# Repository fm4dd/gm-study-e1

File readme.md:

## GM-STUDY-E1

### Description

The gm-study-e1 board is an application module board for the <a href="https://www.colognechip.com/programmable-logic/gatemate-evaluation-board/">GateMate FPGA evaluation board E1</a>, made by <a href="https://www.colognechip.com/">Cologne Chip</a>. It connects to the evaluation board through all six GPIO headers, and its main feature are the input/output components similar to popular FPGA trainer boards used for classroom teaching in electrical engineering and embedded systems education (e.g. Digilent Basys or Altera DE10-lite). These boards were created after successful design tests of the <a href="https://github.com/fm4dd/gm-proto-e1">gm-proto-e1</a> boards. The "gm-proto-e1" boards have only a few basic I/O, but provide a 2.54mm prototyping area for experimentation with GateMate E1.

### Overview

The gm-study-e1 boards provide:
- 4x push buttons
- 10x slide switches
- 10x LED
- 6x 7-Segment display modules (non-multiplexed)
- 1x 4 Khz buzzer
- J1 2.54mm pin header with 5V signal translation

The J1 pin header and pinout can connect 5V HD44780 character LCD display modules, or interface with breadboards for prototyping. There, the FPGA 2.5V IO signals are translated into 5V TTL levels, which can be used with an Arduino.

This design is registered under the OSHWA Open Source Hardware Self-Certification:  

### Hardware Versions

Two board variants have been designed: SMD, using 0.28" SMD 7-Segment modules, and THT for using slightly bigger 0.3" through-hole 7-Segment modules. For THT components, great care needs to be taken to cut pins flush during soldering, and prevent them from reaching components of the evaluation board below. The 1.27mm pitch GPIO connectors are offered with different distance spacers (2, 2.5 and 5mm), and the standard spacers achieve only 5mm total clearance.

Both gm-study-e1 application boards have been designed as a 100x70mm double-layer PCB with precision alignment of the six 46-pin 1.27mm pitch GPIO bank connectors (mates all 276 pins with the GateMate FPGA evaluation board E1 V3.1B).

#### Through-hole Design:

| Version | Gerber | Schema |
|---------|--------|--------|
| 1.1     |[2030325-gm-study-e1-tht-gerber.zip](fabfiles-tht/v11/20230325-gm-study-e1-tht-gerber.zip) | [20230325-gm-proto-e1-schematic.pdf](fabfiles-tht/v11/20230325-gm-study-e1-tht-schematic.pdf) |

#### Surface-Mount Design:

| Version | Gerber | Schema |
|---------|--------|--------|
| 1.1     |[20230326-gm-study-e1-smd-gerber.zip](fabfiles-smd/v11/20230326-gm-study-e1-smd-gerber.zip) | [20230326-gm-study-e1-smd-schematic.pdf](fabfiles-smd/v11/20230326-gm-study-e1-smd-schematic.pdf) |

### Pin Assignments

Both variants (THT and SMD) have identical pinout, listed in [pin-assignment.md](pin-assignment.md).
They share a single constraints assignment file, located here: [gm-study-e1.ccf](examples/gm-study-e1.ccf)

### Example Code

The following code examples demonstrate the board input/output components for quick verification. The code has been tested with the pre-compiled opensource toolchain released through the GateMate support site at <a href="https://www.colognechip.com/mygatemate/">https://www.colognechip.com/mygatemate/</a>

| Language | Folder                   | Description                                                       |
|----------|--------------------------|-------------------------------------------------------------------|
| Verilog  |[blink](examples/blink)   | blinks five LED's in a alternating pattern                        |
| Verilog  |[count](examples/count)   | binary counter displayed on ten LED and six 7-Segment digits      |
| Verilog  |[button](examples/button) | push button press changes LED frequency and light move direction  |
| Verilog  |[switch](examples/switch) | each slide switch turns its corresponding LED on or off           |
| Verilog  |[sound](examples/sound)   | play a song on the buzzer, show notes on LED and 7-segment digits |

### Board Pictures

The gm-study-e1 application board, running the switch demo.

The gm-study-e1 application board has been designed with KiCad version 6.0.

The gm-study-e1 application board, up close.

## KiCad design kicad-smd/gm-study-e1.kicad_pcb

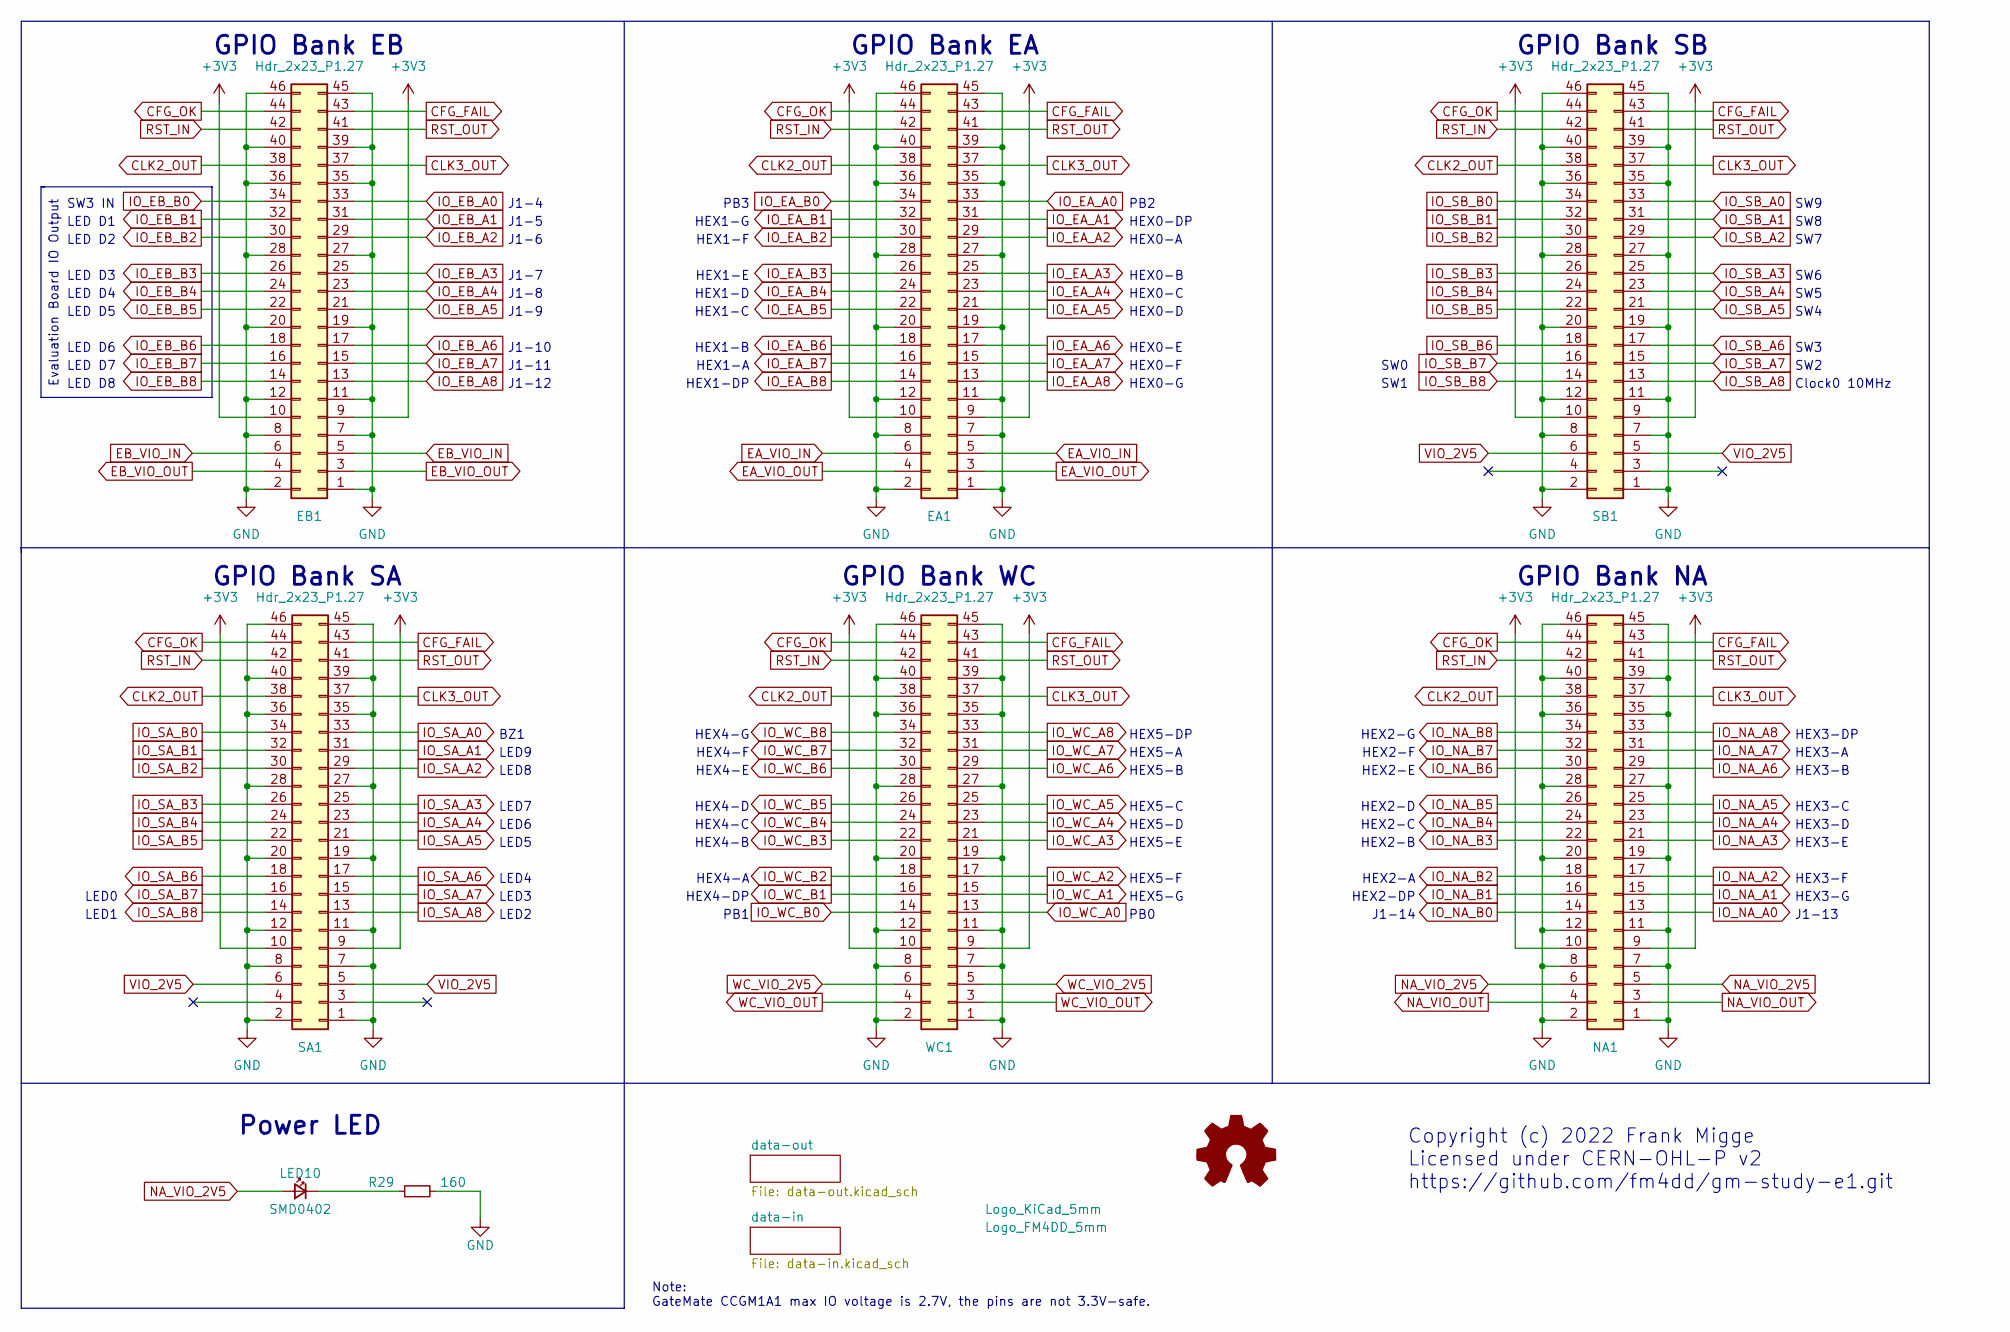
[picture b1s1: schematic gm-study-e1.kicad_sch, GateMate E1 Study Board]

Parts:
EA1: Hdr_2x23_P1.27; PinHeader_2x23_P1.27_backside
EB1: Hdr_2x23_P1.27; PinHeader_2x23_P1.27_backside
LB1: Logo_KiCad_5mm; Logo_KiCad_5mm_SScr
LB2: Label_5V
LB3: Label_GND
LB4: Logo_FM4DD_5mm; Logo_FM4DD_5mm_SScr
LED10: SMD0402; LED_0402_no_frame
NA1: Hdr_2x23_P1.27; PinHeader_2x23_P1.27_backside
R29: 160; R_0402_1005Metric
SA1: Hdr_2x23_P1.27; PinHeader_2x23_P1.27_backside
SB1: Hdr_2x23_P1.27; PinHeader_2x23_P1.27_backside
WC1: Hdr_2x23_P1.27; PinHeader_2x23_P1.27_backside

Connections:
+3V3: EA1.9, EA1.10, EB1.9, EB1.10, NA1.9, NA1.10, SA1.9, SA1.10, SB1.9, SB1.10, WC1.9, WC1.10; also elsewhere on the board
CFG_FAIL: EA1.43, EB1.43, NA1.43, SA1.43, SB1.43, WC1.43
CFG_OK: EA1.44, EB1.44, NA1.44, SA1.44, SB1.44, WC1.44
CLK2_OUT: EA1.38, EB1.38, NA1.38, SA1.38, SB1.38, WC1.38
CLK3_OUT: EA1.37, EB1.37, NA1.37, SA1.37, SB1.37, WC1.37
EA_VIO_IN: EA1.5, EA1.6
EA_VIO_OUT: EA1.3, EA1.4
EB_VIO_IN: EB1.5, EB1.6; also elsewhere on the board
EB_VIO_OUT: EB1.3, EB1.4
GND: EA1.1, EA1.2, EA1.7, EA1.8, EA1.11, EA1.12, EA1.19, EA1.20, EA1.27, EA1.28, EA1.35, EA1.36, EA1.39, EA1.40, EA1.45, EA1.46, EB1.1, EB1.2, EB1.7, EB1.8, EB1.11, EB1.12, EB1.19, EB1.20, EB1.27, EB1.28, EB1.35, EB1.36, EB1.39, EB1.40, EB1.45, EB1.46, NA1.1, NA1.2, NA1.7, NA1.8, NA1.11, NA1.12, NA1.19, NA1.20, NA1.27, NA1.28, NA1.35, NA1.36, NA1.39, NA1.40, NA1.45, NA1.46, R29.2, SA1.1, SA1.2, SA1.7, SA1.8, SA1.11, SA1.12, SA1.19, SA1.20, SA1.27, SA1.28, SA1.35, SA1.36, SA1.39, SA1.40, SA1.45, SA1.46, SB1.1, SB1.2, SB1.7, SB1.8, SB1.11, SB1.12, SB1.19, SB1.20, SB1.27, SB1.28, SB1.35, SB1.36, SB1.39, SB1.40, SB1.45, SB1.46, WC1.1, WC1.2, WC1.7, WC1.8, WC1.11, WC1.12, WC1.19, WC1.20, WC1.27, WC1.28, WC1.35, WC1.36, WC1.39, WC1.40, WC1.45, WC1.46; also elsewhere on the board
IO_EA_A0: EA1.33; also elsewhere on the board
IO_EA_A1: EA1.31; also elsewhere on the board
IO_EA_A2: EA1.29; also elsewhere on the board
IO_EA_A3: EA1.25; also elsewhere on the board
IO_EA_A4: EA1.23; also elsewhere on the board
IO_EA_A5: EA1.21; also elsewhere on the board
IO_EA_A6: EA1.17; also elsewhere on the board
IO_EA_A7: EA1.15; also elsewhere on the board
IO_EA_A8: EA1.13; also elsewhere on the board
IO_EA_B0: EA1.34; also elsewhere on the board
IO_EA_B1: EA1.32; also elsewhere on the board
IO_EA_B2: EA1.30; also elsewhere on the board
IO_EA_B3: EA1.26; also elsewhere on the board
IO_EA_B4: EA1.24; also elsewhere on the board
IO_EA_B5: EA1.22; also elsewhere on the board
IO_EA_B6: EA1.18; also elsewhere on the board
IO_EA_B7: EA1.16; also elsewhere on the board
IO_EA_B8: EA1.14; also elsewhere on the board
IO_EB_A0: EB1.33; also elsewhere on the board
IO_EB_A1: EB1.31; also elsewhere on the board
IO_EB_A2: EB1.29; also elsewhere on the board
IO_EB_A3: EB1.25; also elsewhere on the board
IO_EB_A4: EB1.23; also elsewhere on the board
IO_EB_A5: EB1.21; also elsewhere on the board
IO_EB_A6: EB1.17; also elsewhere on the board
IO_EB_A7: EB1.15; also elsewhere on the board
IO_EB_A8: EB1.13; also elsewhere on the board
IO_EB_B0: EB1.34
IO_EB_B1: EB1.32
IO_EB_B2: EB1.30
IO_EB_B3: EB1.26
IO_EB_B4: EB1.24
IO_EB_B5: EB1.22
IO_EB_B6: EB1.18
IO_EB_B7: EB1.16
IO_EB_B8: EB1.14
IO_NA_A0: NA1.13; also elsewhere on the board
IO_NA_A1: NA1.15; also elsewhere on the board
IO_NA_A2: NA1.17; also elsewhere on the board
IO_NA_A3: NA1.21; also elsewhere on the board
IO_NA_A4: NA1.23; also elsewhere on the board
IO_NA_A5: NA1.25; also elsewhere on the board
IO_NA_A6: NA1.29; also elsewhere on the board
IO_NA_A7: NA1.31; also elsewhere on the board
IO_NA_A8: NA1.33; also elsewhere on the board
IO_NA_B0: NA1.14; also elsewhere on the board
IO_NA_B1: NA1.16; also elsewhere on the board
IO_NA_B2: NA1.18; also elsewhere on the board
IO_NA_B3: NA1.22; also elsewhere on the board
IO_NA_B4: NA1.24; also elsewhere on the board
IO_NA_B5: NA1.26; also elsewhere on the board
IO_NA_B6: NA1.30; also elsewhere on the board
IO_NA_B7: NA1.32; also elsewhere on the board
IO_NA_B8: NA1.34; also elsewhere on the board
IO_SA_A0: SA1.33; also elsewhere on the board
IO_SA_A1: SA1.31; also elsewhere on the board
IO_SA_A2: SA1.29; also elsewhere on the board
IO_SA_A3: SA1.25; also elsewhere on the board
IO_SA_A4: SA1.23; also elsewhere on the board
IO_SA_A5: SA1.21; also elsewhere on the board
IO_SA_A6: SA1.17; also elsewhere on the board
IO_SA_A7: SA1.15; also elsewhere on the board
IO_SA_A8: SA1.13; also elsewhere on the board
IO_SA_B0: SA1.34
IO_SA_B1: SA1.32
IO_SA_B2: SA1.30
IO_SA_B3: SA1.26
IO_SA_B4: SA1.24
IO_SA_B5: SA1.22
IO_SA_B6: SA1.18
IO_SA_B7: SA1.16; also elsewhere on the board
IO_SA_B8: SA1.14; also elsewhere on the board
IO_SB_A0: SB1.33; also elsewhere on the board
IO_SB_A1: SB1.31; also elsewhere on the board
IO_SB_A2: SB1.29; also elsewhere on the board
IO_SB_A3: SB1.25; also elsewhere on the board
IO_SB_A4: SB1.23; also elsewhere on the board
IO_SB_A5: SB1.21; also elsewhere on the board
IO_SB_A6: SB1.17; also elsewhere on the board
IO_SB_A7: SB1.15; also elsewhere on the board
IO_SB_A8: SB1.13
IO_SB_B0: SB1.34
IO_SB_B1: SB1.32
IO_SB_B2: SB1.30
IO_SB_B3: SB1.26
IO_SB_B4: SB1.24
IO_SB_B5: SB1.22
IO_SB_B6: SB1.18
IO_SB_B7: SB1.16; also elsewhere on the board
IO_SB_B8: SB1.14; also elsewhere on the board
IO_WC_A0: WC1.13; also elsewhere on the board
IO_WC_A1: WC1.15; also elsewhere on the board
IO_WC_A2: WC1.17; also elsewhere on the board
IO_WC_A3: WC1.21; also elsewhere on the board
IO_WC_A4: WC1.23; also elsewhere on the board
IO_WC_A5: WC1.25; also elsewhere on the board
IO_WC_A6: WC1.29; also elsewhere on the board
IO_WC_A7: WC1.31; also elsewhere on the board
IO_WC_A8: WC1.33; also elsewhere on the board
IO_WC_B0: WC1.14; also elsewhere on the board
IO_WC_B1: WC1.16; also elsewhere on the board
IO_WC_B2: WC1.18; also elsewhere on the board
IO_WC_B3: WC1.22; also elsewhere on the board
IO_WC_B4: WC1.24; also elsewhere on the board
IO_WC_B5: WC1.26; also elsewhere on the board
IO_WC_B6: WC1.30; also elsewhere on the board
IO_WC_B7: WC1.32; also elsewhere on the board
IO_WC_B8: WC1.34; also elsewhere on the board
NA_VIO_2V5: LED10.2 (A), NA1.5, NA1.6
NA_VIO_OUT: NA1.3, NA1.4
unnamed: LED10.1 (K), R29.1
RST_IN: EA1.42, EB1.42, NA1.42, SA1.42, SB1.42, WC1.42
RST_OUT: EA1.41, EB1.41, NA1.41, SA1.41, SB1.41, WC1.41
VIO_2V5: SA1.5, SA1.6, SB1.5, SB1.6; also elsewhere on the board
WC_VIO_2V5: WC1.5, WC1.6
WC_VIO_OUT: WC1.3, WC1.4

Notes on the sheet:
HEX1-A
BZ1
SW3
PB0
LED7
HEX5-C
SW7
HEX1-B
HEX1-E
LED D3
Note: GateMate CCGM1A1 max IO voltage is 2.7V, the pins are not 3.3V-safe.
LED D7
HEX3-B
SW4
LED D2
SW8
HEX0-F
J1-7
HEX5-A
J1-10
HEX4-D
HEX5-E
SW3 IN
HEX4-F
HEX1-F
SW0
SW1
LED D8
HEX3-C
Clock0 10MHz
LED D4
HEX3-DP
SW6
HEX0-G
J1-6
HEX2-DP
GPIO Bank NA
LED0
Evaluation Board IO Output
HEX3-A

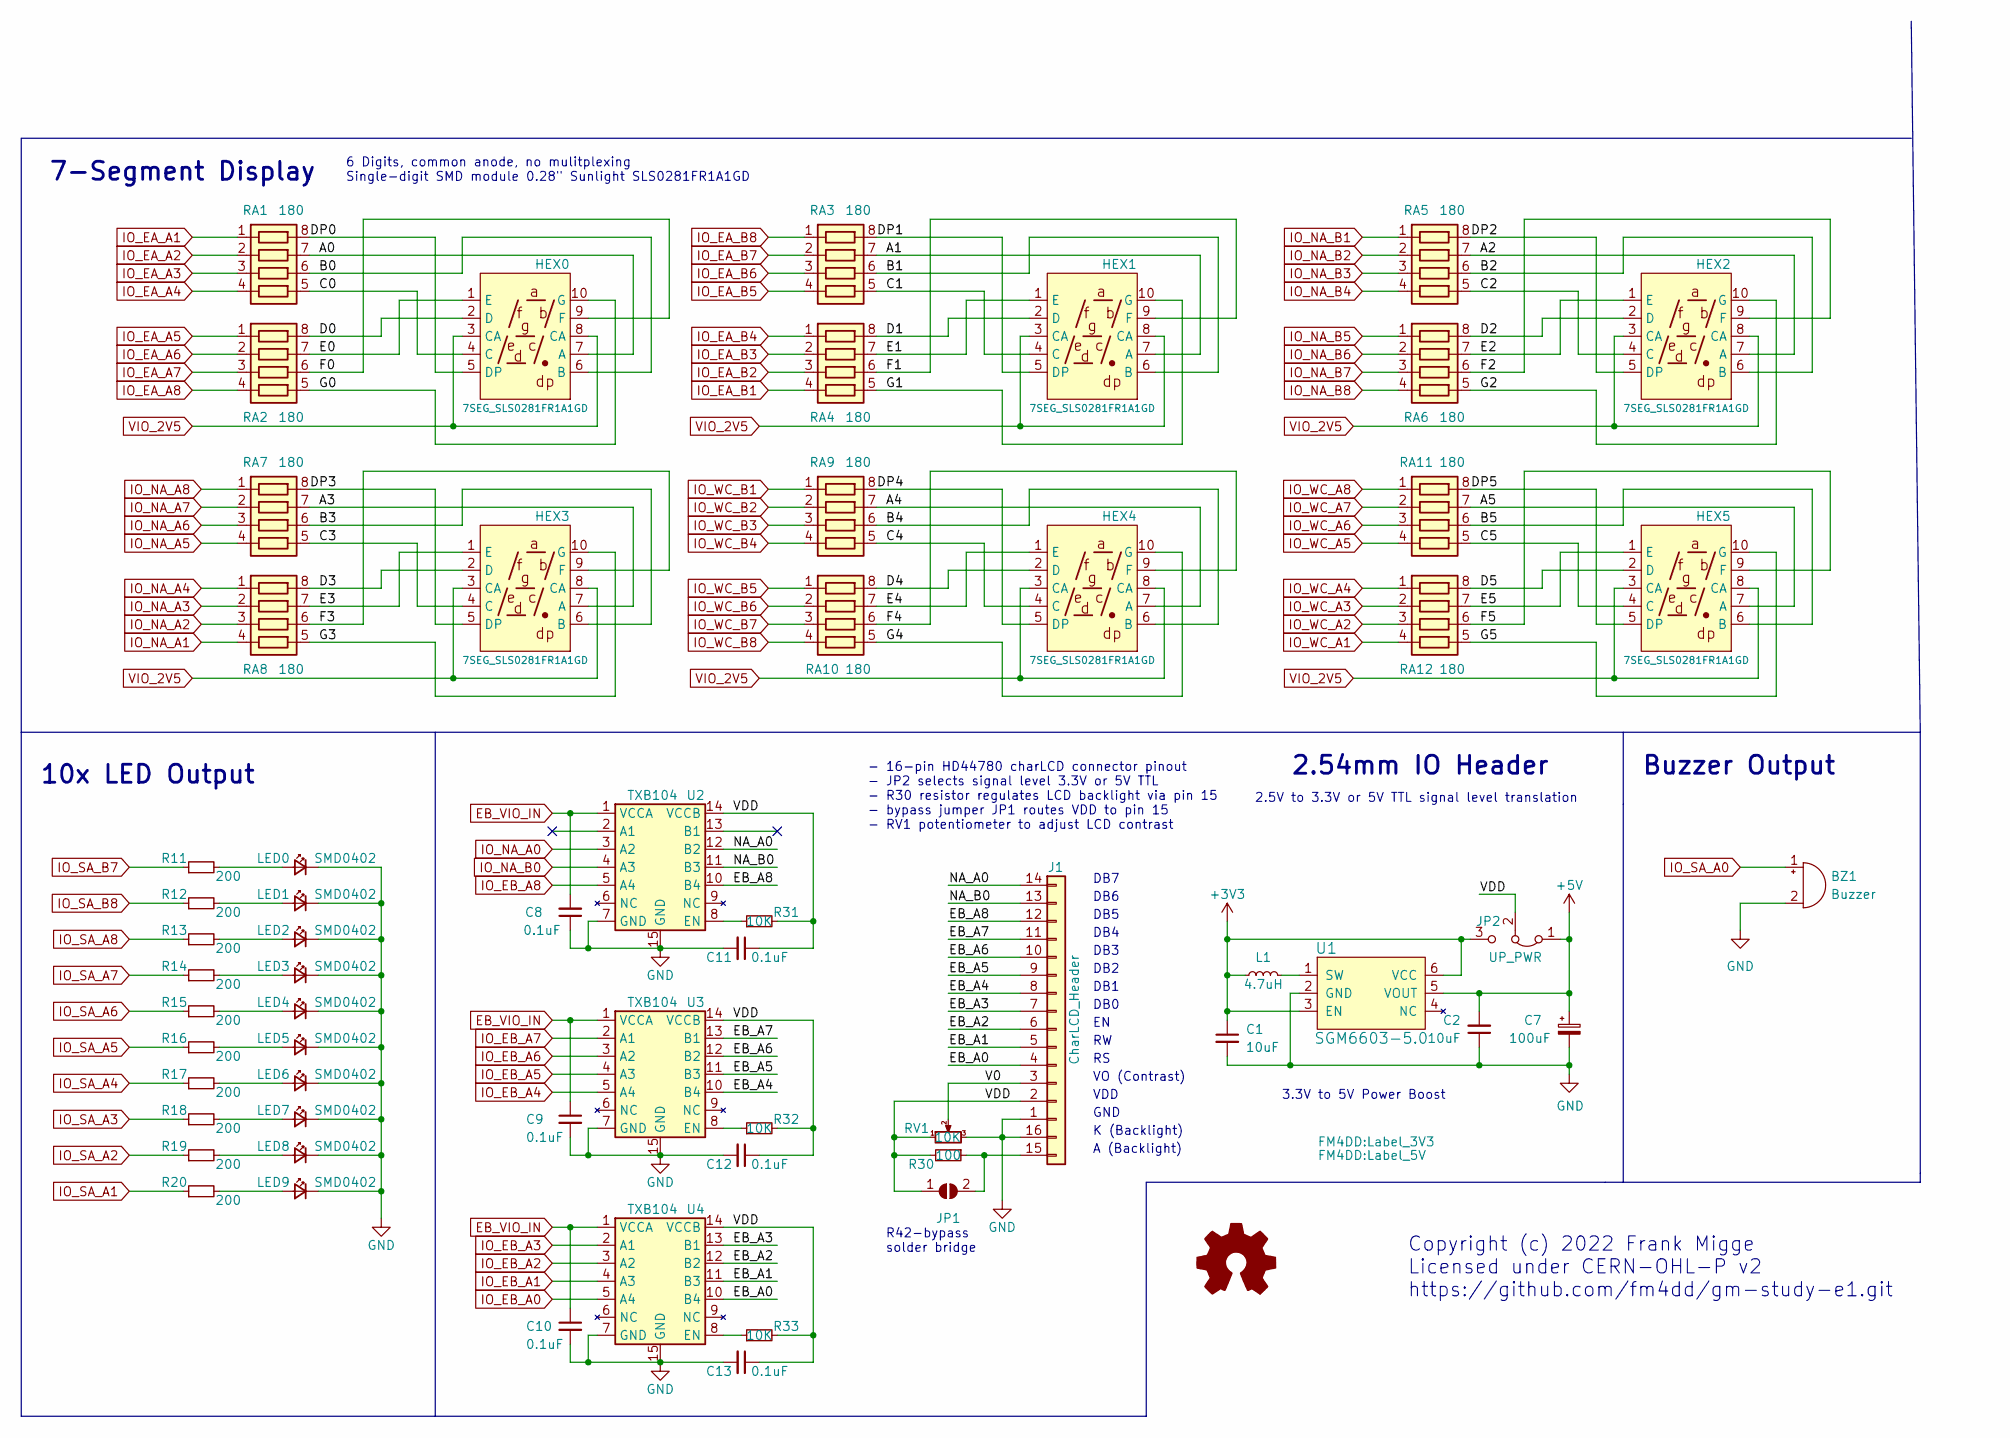
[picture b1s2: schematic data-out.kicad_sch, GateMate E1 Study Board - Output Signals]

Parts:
BZ1: Buzzer; Buzzer_Murata_PKLCS1212E
C1, C2: 10uF; C_0402_1005Metric
C7: 100uF; CP_Elec_6.3x5.3
C8, C9, C10, C11, C12, C13: 0.1uF; C_0402_1005Metric
HEX0, HEX1, HEX2, HEX3, HEX4, HEX5: 7SEG_SLS0281FR1A1GD; 7SEG SMD SLS0281FR1A1GD
J1: CharLCD_Header; CharLCD Header
JP1: SolderJumper_2_Open; SolderJumper-2_P1.3mm_Open_Pad1.0x1.5mm
JP2: UP_PWR; PinHeader_1x03_P2.54mm_Vertical
L1: 4.7uH; L_0603_1608Metric
LB5: Label_3V3
LB6: Label_5V
LED0, LED1, LED2, LED3, LED4, LED5, LED6, LED7, LED8, LED9: SMD0402; LED_0402_FPGA
R11, R12, R13, R14, R15, R16, R17, R18, R19, R20: 200; R_0402_1005Metric
R30: 100; R_0402_1005Metric
R31, R32, R33: 10K; R_0402_1005Metric
RA1, RA2, RA3, RA4, RA5, RA6, RA7, RA8, RA9, RA10, RA11, RA12: 180; R_Array_Convex_4x0603
RV1: 10K; Potentiometer_Bourns_3362P_Vertical
U1: SGM6603-5.0; SOT-23-6
U2, U3, U4: TXB104; S-PVQFN-N14-1EP_3.65x3.65_P0.5_EP2.05x2.05

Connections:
+3V3: C1.1, JP2.3 (B), L1.1, U1.3 (EN), U1.6 (VCC); also elsewhere on the board
+5V: C2.2, C7.1, JP2.1 (A), U1.5 (VOUT)
/data-out/A0: HEX0.7 (A), RA1.7 (R2)
/data-out/A1: HEX1.7 (A), RA3.7 (R2)
/data-out/A2: HEX2.7 (A), RA5.7 (R2)
/data-out/A3: HEX3.7 (A), RA7.7 (R2)
/data-out/A4: HEX4.7 (A), RA9.7 (R2)
/data-out/A5: HEX5.7 (A), RA11.7 (R2)
/data-out/B0: HEX0.6 (B), RA1.6 (R3)
/data-out/B1: HEX1.6 (B), RA3.6 (R3)
/data-out/B2: HEX2.6 (B), RA5.6 (R3)
/data-out/B3: HEX3.6 (B), RA7.6 (R3)
/data-out/B4: HEX4.6 (B), RA9.6 (R3)
/data-out/B5: HEX5.6 (B), RA11.6 (R3)
/data-out/C0: HEX0.4 (C), RA1.5 (R4)
/data-out/C1: HEX1.4 (C), RA3.5 (R4)
/data-out/C2: HEX2.4 (C), RA5.5 (R4)
/data-out/C3: HEX3.4 (C), RA7.5 (R4)
/data-out/C4: HEX4.4 (C), RA9.5 (R4)
/data-out/C5: HEX5.4 (C), RA11.5 (R4)
/data-out/D0: HEX0.2 (D), RA2.8 (R1)
/data-out/D1: HEX1.2 (D), RA4.8 (R1)
/data-out/D2: HEX2.2 (D), RA6.8 (R1)
/data-out/D3: HEX3.2 (D), RA8.8 (R1)
/data-out/D4: HEX4.2 (D), RA10.8 (R1)
/data-out/D5: HEX5.2 (D), RA12.8 (R1)
/data-out/DP0: HEX0.5 (DP), RA1.8 (R1)
/data-out/DP1: HEX1.5 (DP), RA3.8 (R1)
/data-out/DP2: HEX2.5 (DP), RA5.8 (R1)
/data-out/DP3: HEX3.5 (DP), RA7.8 (R1)
/data-out/DP4: HEX4.5 (DP), RA9.8 (R1)
/data-out/DP5: HEX5.5 (DP), RA11.8 (R1)
/data-out/E0: HEX0.1 (E), RA2.7 (R2)
/data-out/E1: HEX1.1 (E), RA4.7 (R2)
/data-out/E2: HEX2.1 (E), RA6.7 (R2)
/data-out/E3: HEX3.1 (E), RA8.7 (R2)
/data-out/E4: HEX4.1 (E), RA10.7 (R2)
/data-out/E5: HEX5.1 (E), RA12.7 (R2)
/data-out/EB_A0: J1.4, U4.10 (B4)
/data-out/EB_A1: J1.5, U4.11 (B3)
/data-out/EB_A2: J1.6, U4.12 (B2)
/data-out/EB_A3: J1.7, U4.13 (B1)
/data-out/EB_A4: J1.8, U3.10 (B4)
/data-out/EB_A5: J1.9, U3.11 (B3)
/data-out/EB_A6: J1.10, U3.12 (B2)
/data-out/EB_A7: J1.11, U3.13 (B1)
/data-out/EB_A8: J1.12, U2.10 (B4)
/data-out/F0: HEX0.9 (F), RA2.6 (R3)
/data-out/F1: HEX1.9 (F), RA4.6 (R3)
/data-out/F2: HEX2.9 (F), RA6.6 (R3)
/data-out/F3: HEX3.9 (F), RA8.6 (R3)
/data-out/F4: HEX4.9 (F), RA10.6 (R3)
/data-out/F5: HEX5.9 (F), RA12.6 (R3)
/data-out/G0: HEX0.10 (G), RA2.5 (R4)
/data-out/G1: HEX1.10 (G), RA4.5 (R4)
/data-out/G2: HEX2.10 (G), RA6.5 (R4)
/data-out/G3: HEX3.10 (G), RA8.5 (R4)
/data-out/G4: HEX4.10 (G), RA10.5 (R4)
/data-out/G5: HEX5.10 (G), RA12.5 (R4)
/data-out/NA_A0: J1.14, U2.12 (B2)
/data-out/NA_B0: J1.13, U2.11 (B3)
/data-out/V0: J1.3, RV1.2
/data-out/VDD: C11.1, C12.1, C13.1, J1.2, JP1.1 (A), JP2.2 (C), R30.2, R31.2, R32.2, R33.2, RV1.1, U2.14 (VCCB), U3.14 (VCCB), U4.14 (VCCB)
EB_VIO_IN: C8.2, C9.1, C10.1, U2.1 (VCCA), U3.1 (VCCA), U4.1 (VCCA); also elsewhere on the board
GND: BZ1.2 (+), C1.2, C2.1, C7.2, C8.1, C9.2, C10.2, C11.2, C12.2, C13.2, J1.1, J1.16, LED0.1 (K), LED1.1 (K), LED2.1 (K), LED3.1 (K), LED4.1 (K), LED5.1 (K), LED6.1 (K), LED7.1 (K), LED8.1 (K), LED9.1 (K), RV1.3, U1.2 (GND), U2.7 (GND), U2.15 (GND), U3.7 (GND), U3.15 (GND), U4.7 (GND), U4.15 (GND); also elsewhere on the board
IO_EA_A1: RA1.1 (R1); also elsewhere on the board
IO_EA_A2: RA1.2 (R2); also elsewhere on the board
IO_EA_A3: RA1.3 (R3); also elsewhere on the board
IO_EA_A4: RA1.4 (R4); also elsewhere on the board
IO_EA_A5: RA2.1 (R1); also elsewhere on the board
IO_EA_A6: RA2.2 (R2); also elsewhere on the board
IO_EA_A7: RA2.3 (R3); also elsewhere on the board
IO_EA_A8: RA2.4 (R4); also elsewhere on the board
IO_EA_B1: RA4.4 (R4); also elsewhere on the board
IO_EA_B2: RA4.3 (R3); also elsewhere on the board
IO_EA_B3: RA4.2 (R2); also elsewhere on the board
IO_EA_B4: RA4.1 (R1); also elsewhere on the board
IO_EA_B5: RA3.4 (R4); also elsewhere on the board
IO_EA_B6: RA3.3 (R3); also elsewhere on the board
IO_EA_B7: RA3.2 (R2); also elsewhere on the board
IO_EA_B8: RA3.1 (R1); also elsewhere on the board
IO_EB_A0: U4.5 (A4); also elsewhere on the board
IO_EB_A1: U4.4 (A3); also elsewhere on the board
IO_EB_A2: U4.3 (A2); also elsewhere on the board
IO_EB_A3: U4.2 (A1); also elsewhere on the board
IO_EB_A4: U3.5 (A4); also elsewhere on the board
IO_EB_A5: U3.4 (A3); also elsewhere on the board
IO_EB_A6: U3.3 (A2); also elsewhere on the board
IO_EB_A7: U3.2 (A1); also elsewhere on the board
IO_EB_A8: U2.5 (A4); also elsewhere on the board
IO_NA_A0: U2.3 (A2); also elsewhere on the board
IO_NA_A1: RA8.4 (R4); also elsewhere on the board
IO_NA_A2: RA8.3 (R3); also elsewhere on the board
IO_NA_A3: RA8.2 (R2); also elsewhere on the board
IO_NA_A4: RA8.1 (R1); also elsewhere on the board
IO_NA_A5: RA7.4 (R4); also elsewhere on the board
IO_NA_A6: RA7.3 (R3); also elsewhere on the board
IO_NA_A7: RA7.2 (R2); also elsewhere on the board
IO_NA_A8: RA7.1 (R1); also elsewhere on the board
IO_NA_B0: U2.4 (A3); also elsewhere on the board
IO_NA_B1: RA5.1 (R1); also elsewhere on the board
IO_NA_B2: RA5.2 (R2); also elsewhere on the board
IO_NA_B3: RA5.3 (R3); also elsewhere on the board
IO_NA_B4: RA5.4 (R4); also elsewhere on the board
IO_NA_B5: RA6.1 (R1); also elsewhere on the board
IO_NA_B6: RA6.2 (R2); also elsewhere on the board
IO_NA_B7: RA6.3 (R3); also elsewhere on the board
IO_NA_B8: RA6.4 (R4); also elsewhere on the board
IO_SA_A0: BZ1.1 (-); also elsewhere on the board
IO_SA_A1: R20.1; also elsewhere on the board
IO_SA_A2: R19.1; also elsewhere on the board
IO_SA_A3: R18.1; also elsewhere on the board
IO_SA_A4: R17.1; also elsewhere on the board
IO_SA_A5: R16.1; also elsewhere on the board
IO_SA_A6: R15.1; also elsewhere on the board
IO_SA_A7: R14.1; also elsewhere on the board
IO_SA_A8: R13.1; also elsewhere on the board
IO_SA_B7: R11.1; also elsewhere on the board
IO_SA_B8: R12.1; also elsewhere on the board
IO_WC_A1: RA12.4 (R4); also elsewhere on the board
IO_WC_A2: RA12.3 (R3); also elsewhere on the board
IO_WC_A3: RA12.2 (R2); also elsewhere on the board
IO_WC_A4: RA12.1 (R1); also elsewhere on the board
IO_WC_A5: RA11.4 (R4); also elsewhere on the board
IO_WC_A6: RA11.3 (R3); also elsewhere on the board
IO_WC_A7: RA11.2 (R2); also elsewhere on the board
IO_WC_A8: RA11.1 (R1); also elsewhere on the board
IO_WC_B1: RA9.1 (R1); also elsewhere on the board
IO_WC_B2: RA9.2 (R2); also elsewhere on the board
IO_WC_B3: RA9.3 (R3); also elsewhere on the board
IO_WC_B4: RA9.4 (R4); also elsewhere on the board
IO_WC_B5: RA10.1 (R1); also elsewhere on the board
IO_WC_B6: RA10.2 (R2); also elsewhere on the board
IO_WC_B7: RA10.3 (R3); also elsewhere on the board
IO_WC_B8: RA10.4 (R4); also elsewhere on the board
unnamed: J1.15, JP1.2 (B), R30.1
unnamed: LED0.2 (A), R11.2
unnamed: LED1.2 (A), R12.2
unnamed: LED2.2 (A), R13.2
unnamed: LED3.2 (A), R14.2
unnamed: LED4.2 (A), R15.2
unnamed: LED5.2 (A), R16.2
unnamed: LED6.2 (A), R17.2
unnamed: LED7.2 (A), R18.2
unnamed: LED8.2 (A), R19.2
unnamed: LED9.2 (A), R20.2
unnamed: L1.2, U1.1 (SW)
unnamed: R31.1, U2.8 (EN)
unnamed: R32.1, U3.8 (EN)
unnamed: R33.1, U4.8 (EN)
VIO_2V5: HEX0.3 (CA), HEX0.8 (CA), HEX1.3 (CA), HEX1.8 (CA), HEX2.3 (CA), HEX2.8 (CA), HEX3.3 (CA), HEX3.8 (CA), HEX4.3 (CA), HEX4.8 (CA), HEX5.3 (CA), HEX5.8 (CA); also elsewhere on the board

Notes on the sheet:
10x LED Output
2.54mm IO Header
K (Backlight)
3.3V to 5V Power Boost
DB3
DB0
A (Backlight)
VO (Contrast)
DB7
Copyright (c) 2022 Frank Migge Licensed under CERN-OHL-P v2 https://github.com/fm4dd/gm-study-e1.git
DB1
R42-bypass solder bridge
VDD
2.5V to 3.3V or 5V TTL signal level translation
6 Digits, common anode, no mulitplexing Single-digit SMD module 0.28" Sunlight SLS0281FR1A1GD
GND
DB4
- 16-pin HD44780 charLCD connector pinout - JP2 selects signal level 3.3V or 5V TTL - R30 resistor regulates LCD backlight via pin 15 - bypass jumper JP1 routes VDD to pin 15 - RV1 potentiometer to adjust LCD contrast
DB6
7-Segment Display
DB2
Buzzer Output
DB5

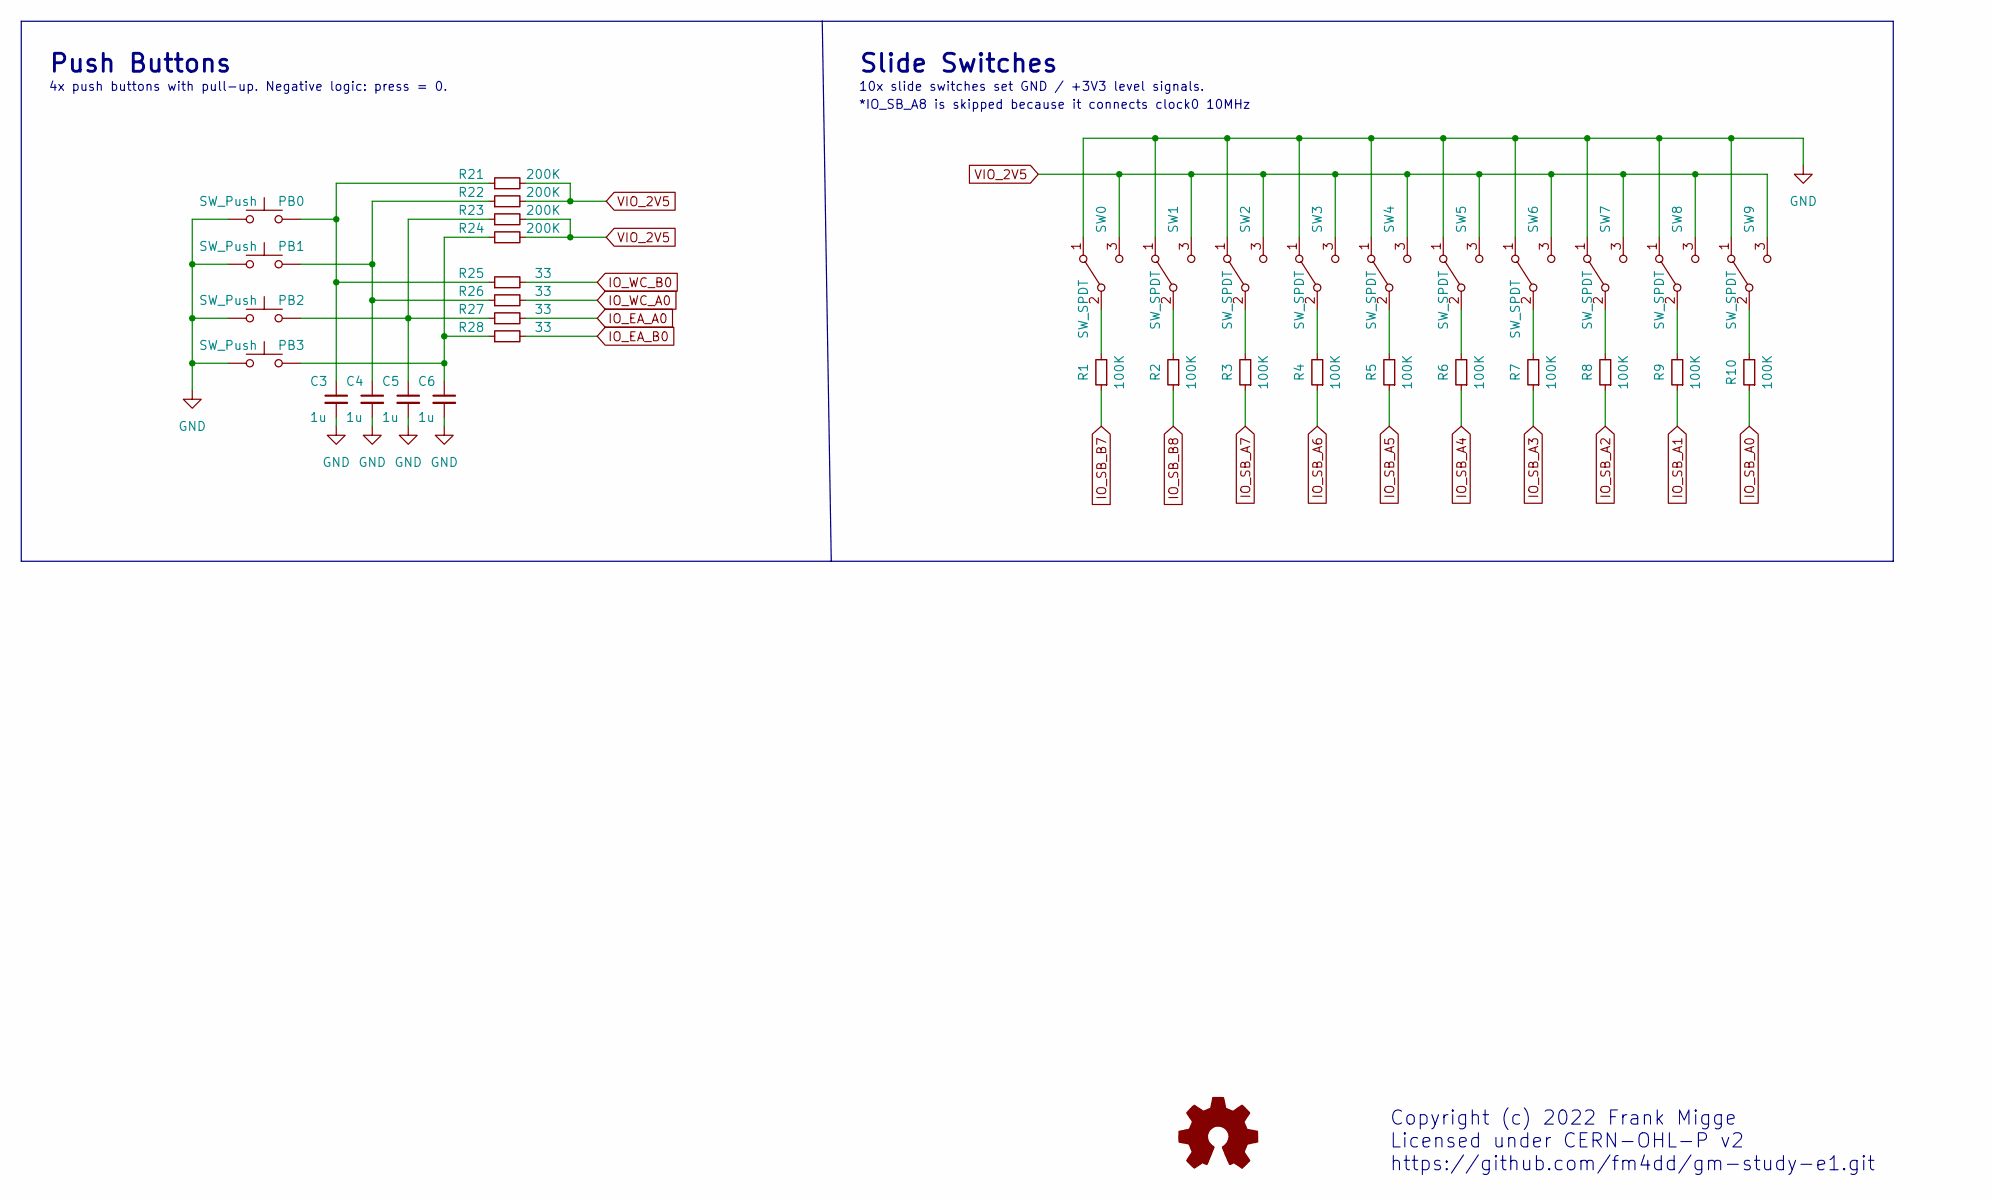
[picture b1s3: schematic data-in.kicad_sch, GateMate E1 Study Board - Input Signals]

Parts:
C3, C4, C5, C6: 1u; C_0402_1005Metric
PB0, PB1, PB2, PB3: SW_Push; SW_PUSH_6mm
R1, R2, R3, R4, R5, R6, R7, R8, R9, R10: 100K; R_0402_1005Metric
R21, R22, R23, R24: 200K; R_0402_1005Metric
R25, R26, R27, R28: 33; R_0402_1005Metric
SW0, SW1, SW2, SW3, SW4, SW5, SW6, SW7, SW8, SW9: SW_SPDT; SlideSW_SS12-D01

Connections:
GND: C3.2, C4.2, C5.2, C6.2, PB0.1, PB1.1, PB2.1, PB3.1, SW0.1 (A), SW1.1 (A), SW2.1 (A), SW3.1 (A), SW4.1 (A), SW5.1 (A), SW6.1 (A), SW7.1 (A), SW8.1 (A), SW9.1 (A); also elsewhere on the board
IO_EA_A0: R27.2; also elsewhere on the board
IO_EA_B0: R28.2; also elsewhere on the board
IO_SB_A0: R10.1; also elsewhere on the board
IO_SB_A1: R9.1; also elsewhere on the board
IO_SB_A2: R8.1; also elsewhere on the board
IO_SB_A3: R7.1; also elsewhere on the board
IO_SB_A4: R6.1; also elsewhere on the board
IO_SB_A5: R5.1; also elsewhere on the board
IO_SB_A6: R4.1; also elsewhere on the board
IO_SB_A7: R3.1; also elsewhere on the board
IO_SB_B7: R1.1; also elsewhere on the board
IO_SB_B8: R2.1; also elsewhere on the board
IO_WC_A0: R26.2; also elsewhere on the board
IO_WC_B0: R25.2; also elsewhere on the board
unnamed: C3.1, PB0.2, R21.1, R25.1
unnamed: C4.1, PB1.2, R22.1, R26.1
unnamed: C5.1, PB2.2, R23.1, R27.1
unnamed: C6.1, PB3.2, R24.1, R28.1
unnamed: R1.2, SW0.2 (B)
unnamed: R2.2, SW1.2 (B)
unnamed: R3.2, SW2.2 (B)
unnamed: R4.2, SW3.2 (B)
unnamed: R5.2, SW4.2 (B)
unnamed: R6.2, SW5.2 (B)
unnamed: R7.2, SW6.2 (B)
unnamed: R8.2, SW7.2 (B)
unnamed: R9.2, SW8.2 (B)
unnamed: R10.2, SW9.2 (B)
VIO_2V5: R21.2, R22.2, R23.2, R24.2, SW0.3 (C), SW1.3 (C), SW2.3 (C), SW3.3 (C), SW4.3 (C), SW5.3 (C), SW6.3 (C), SW7.3 (C), SW8.3 (C), SW9.3 (C); also elsewhere on the board

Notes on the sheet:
Copyright (c) 2022 Frank Migge Licensed under CERN-OHL-P v2 https://github.com/fm4dd/gm-study-e1.git
4x push buttons with pull-up. Negative logic: press = 0.
Push Buttons
10x slide switches set GND / +3V3 level signals.
Slide Switches
*IO_SB_A8 is skipped because it connects clock0 10MHz

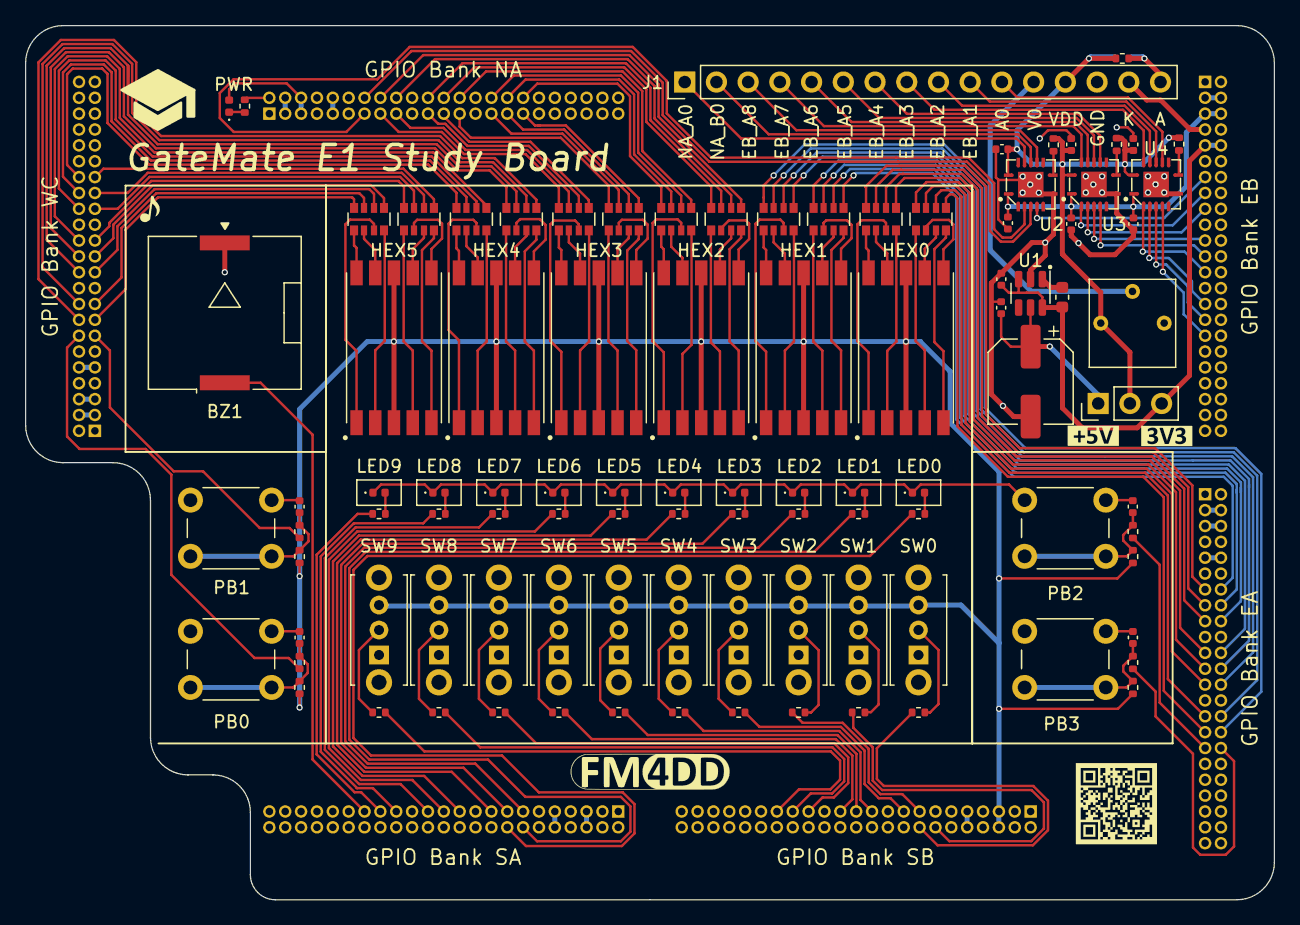
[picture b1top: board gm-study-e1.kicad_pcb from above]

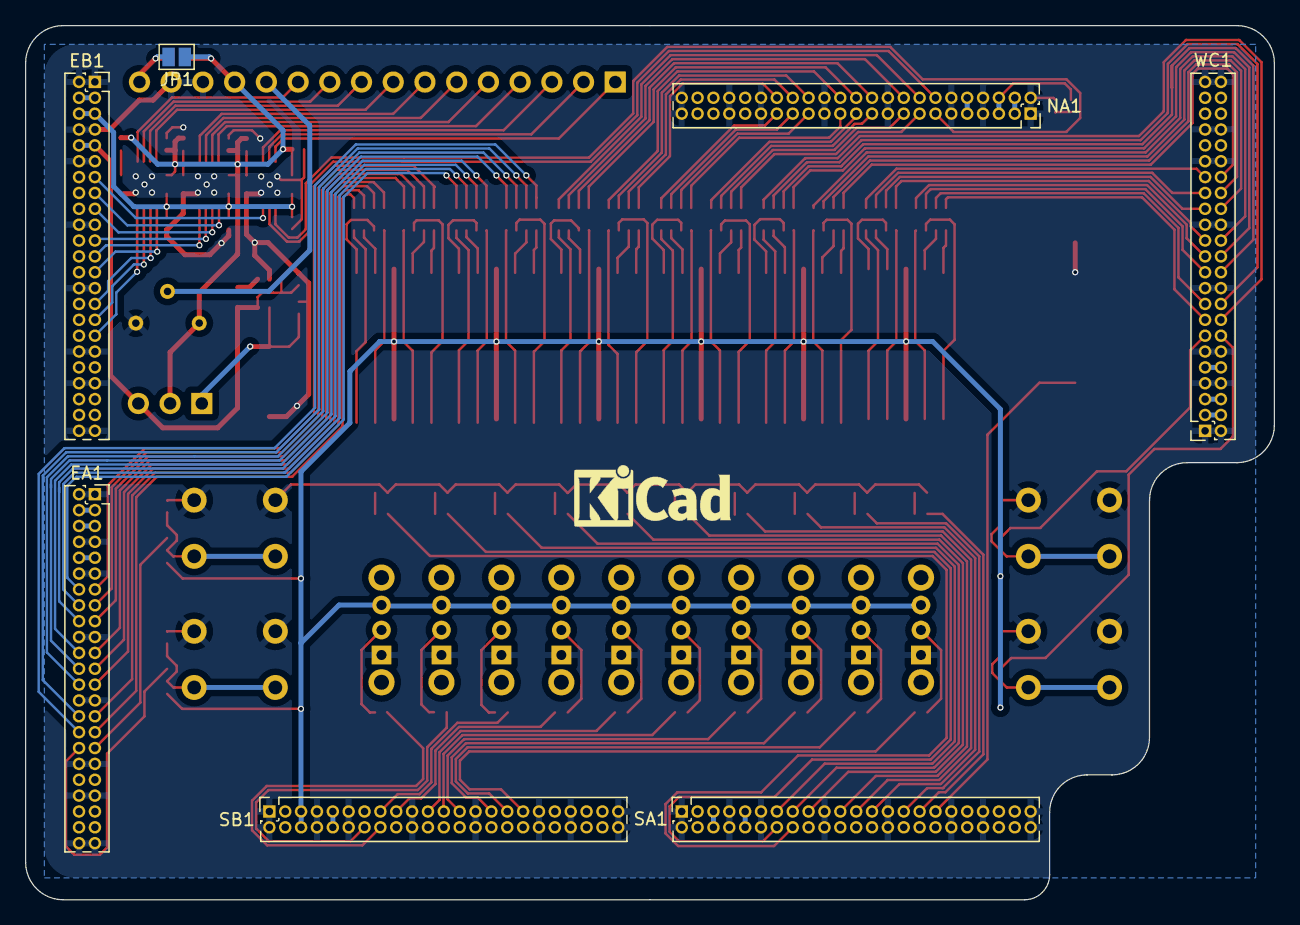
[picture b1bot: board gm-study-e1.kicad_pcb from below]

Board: 2 copper layers, 100.0 x 70.0 mm, 111 parts (8 on the bottom side), 193 nets.

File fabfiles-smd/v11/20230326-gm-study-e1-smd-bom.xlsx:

Comment | Designator | Footprint | JLCPCB Part #（optional）
BZ1 PKLCS1212E4001-R1 | BZ1 | Buzzer_Murata_PKLCS1212E | C113159
10uF 0402CG150J500NT | C1,C2 | C_0402_1005Metric | C30274
1u C0402C104K4RECAUTO | C3,C4,C5,C6 | C_0402_1005Metric | C52923
100uF | C7 | CP_Elec_6.3x5.3 | C134749
0.1u C0402C103K4RECAUTO | C8,C9,C10,C11,C12,C13 | C_0402_1005Metric | C1525
100K 0402WGF1003TCE | R1,R2,R3,R4,R5,R6,R7,R8,R9,R10 | R_0402_1005Metric | C25741
200R 0402WGF2000TCE | R11,R12,R13,R14,R15,R16,R17,R18,R19,R20 | R_0402_1005Metric | C25087
200K 0402WGF2003TCE | R21,R22,R23,R24 | R_0402_1005Metric | C25764
33R 0402WGF330JTCE | R25,R26,R27,R28 | R_0402_1005Metric | C25105
160R 0402WGF1600TCE | R29 | R_0402_1005Metric | C270641
100R | R30 | R_0402_1005Metric | C25076
10K | R31,R32,R33 | R_0402_1005Metric | C25744
180R 4D03WGJ0181T5E | RA1,RA2,RA3,RA4,RA5,RA6,RA7,RA8,RA9,RA10,RA11,RA12 | R_Array_Concave_4x0603 0603_X4 | C12003
SGM6603-5.0 | U1 | SOT-23-6 | C79689
TXB0104 | U2,U3,U4 | S-PVQFN-N14-1EP_3.65x3.65_P0.5_EP2.05x2.05 | C400708
red TJ-S1005SW4TGLC2R-A5 | LED0,LED1,LED2,LED3,LED4,LED5,LED6,LED7,LED8,LED9 | LED_0402_FPGA | C273598
green TJ-S1005SW4TGLC7K-A5 | LED10 | LED_0402_FPGA | C273601
4.7uH | L1 | L_0603_1608Metric | C1034
7SEG SMD SLS0281FR1A1GD | HEX0,HEX1,HEX2,HEX3,HEX4,HEX5 | 7SEG SMD SLS0281FR1A1GD | C225994

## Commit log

2022-09-25 repo init
2022-10-01 verilog examples
2022-10-16 file updates
2022-10-23 add OSHW cert, sound demo
2023-03-26 New THT PCB v1.1 updates J1 level translation IC
2023-03-26 New SMB PCB v1.1 updates J1 level translation IC
